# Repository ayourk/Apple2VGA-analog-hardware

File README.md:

# Clone of ∀2 Retro Computing Analog VGA Card & PicoPal

Design files for the ∀2 Analog series of VGA cards

## Description
Modified version of V2RetroComputing's Apple II Analog VGA Expansion Board using KiCAD 6.0.x. <br />
Changes from original:
* Moved solder jumpers to the back of the board for both the (lack of) PAL/GAL and non WiFi Pico.
* Reorganized Schematic to more easily generate a BOM with Part numbers from LSCS, DigiKey, and Mouser.
* Adopted Hans Hübner's VGA port connector break-away feature. Also reworked board to be 2 layers vs 4 layers but kept 4x bus transcievers vs Han's 2 since the chip in the 4x variant is easier to obtain.
* Added a PLCC socket for the PAL/GAL chip that is getting difficult to find.  Be sure to bridge the solder jumper on the back if you don't plan to populate this socket.
* Re-adjusted layout to provide more Analog VGA signal clarity by making the traces as short as possible between the VGA port connector and the PICO.
* Switched from IDC header style to a shielded FPC cable for less chance of signal interference when using the optional break-away feature.
* Rounded off PCB corners where it made sense.  I hate getting stabbed by PCBs (Grrrr)!

This board should still be binary compatible with the software this hardware was forked from.

### PCB Layout

### See Also
https://github.com/V2RetroComputing/analog <br />
https://github.com/ayourk/Apple2Analog-VGA <br />
https://github.com/hanshuebner/AppleII-VGA <br />
https://github.com/markadev/AppleII-VGA <br />
[Apple II Expansion Card Size Specifications](V2A-Rev1/docs/Apple_II_ExpansionCard_Spec.txt) <br />
[Apple II Expansion Slot Pinout](V2A-Rev1/docs/Apple2SlotPinout.html) <br />
[Apple II Hardware Reference](V2A-Rev1/docs/Apple2HardwareReference.pdf) <br />
https://github.com/ayourk/Apple2Proto <br />

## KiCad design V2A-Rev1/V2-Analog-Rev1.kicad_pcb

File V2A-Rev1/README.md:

# Apple2Proto
Design files for the ∀2 Analog series of VGA cards

## Description
Modified version of V2RetroComputing's Apple II Analog VGA Expansion Board using KiCAD 6.0.x. <br />
Changes from original:
* Moved solder jumpers to the back of the board for both the (lack of) PAL/GAL and non WiFi Pico.
* Reorganized Schematic to more easily generate a BOM with Part numbers from LSCS, DigiKey, and Mouser.
* Adopted Hans Hübner's VGA port connector break-away feature. Also reworked board to be 2 layers vs 4 layers but kept 4x bus transcievers vs Han's 2 since the chip in the 4x variant is easier to obtain.
* Added a PLCC socket for the PAL/GAL chip that is getting difficult to find.  Be sure to bridge the solder jumper on the back if you don't plan to populate this socket.
* Re-adjusted layout to provide more Analog VGA signal clarity by making the traces as short as possible between the VGA port connector and the PICO.
* Switched from IDC header style to a shielded FPC cable for less chance of signal interference when using the optional break-away feature.
* Rounded off PCB corners where it made sense.  I hate getting stabbed by PCBs (Grrrr)!

This board should still be binary compatible with the software this hardware was forked from.

### PCB Layout

### See Also
https://github.com/V2RetroComputing/analog <br />
https://github.com/ayourk/Apple2Analog-VGA <br />
https://github.com/hanshuebner/AppleII-VGA <br />
[Apple II Expansion Card Size Specifications](V2A-Rev1/docs/Apple_II_ExpansionCard_Spec.txt) <br />
[Apple II Expansion Slot Pinout](V2A-Rev1/docs/Apple2SlotPinout.html) <br />
[Apple II Hardware Reference](V2A-Rev1/docs/Apple2HardwareReference.pdf) <br />
https://github.com/ayourk/Apple2Proto <br />

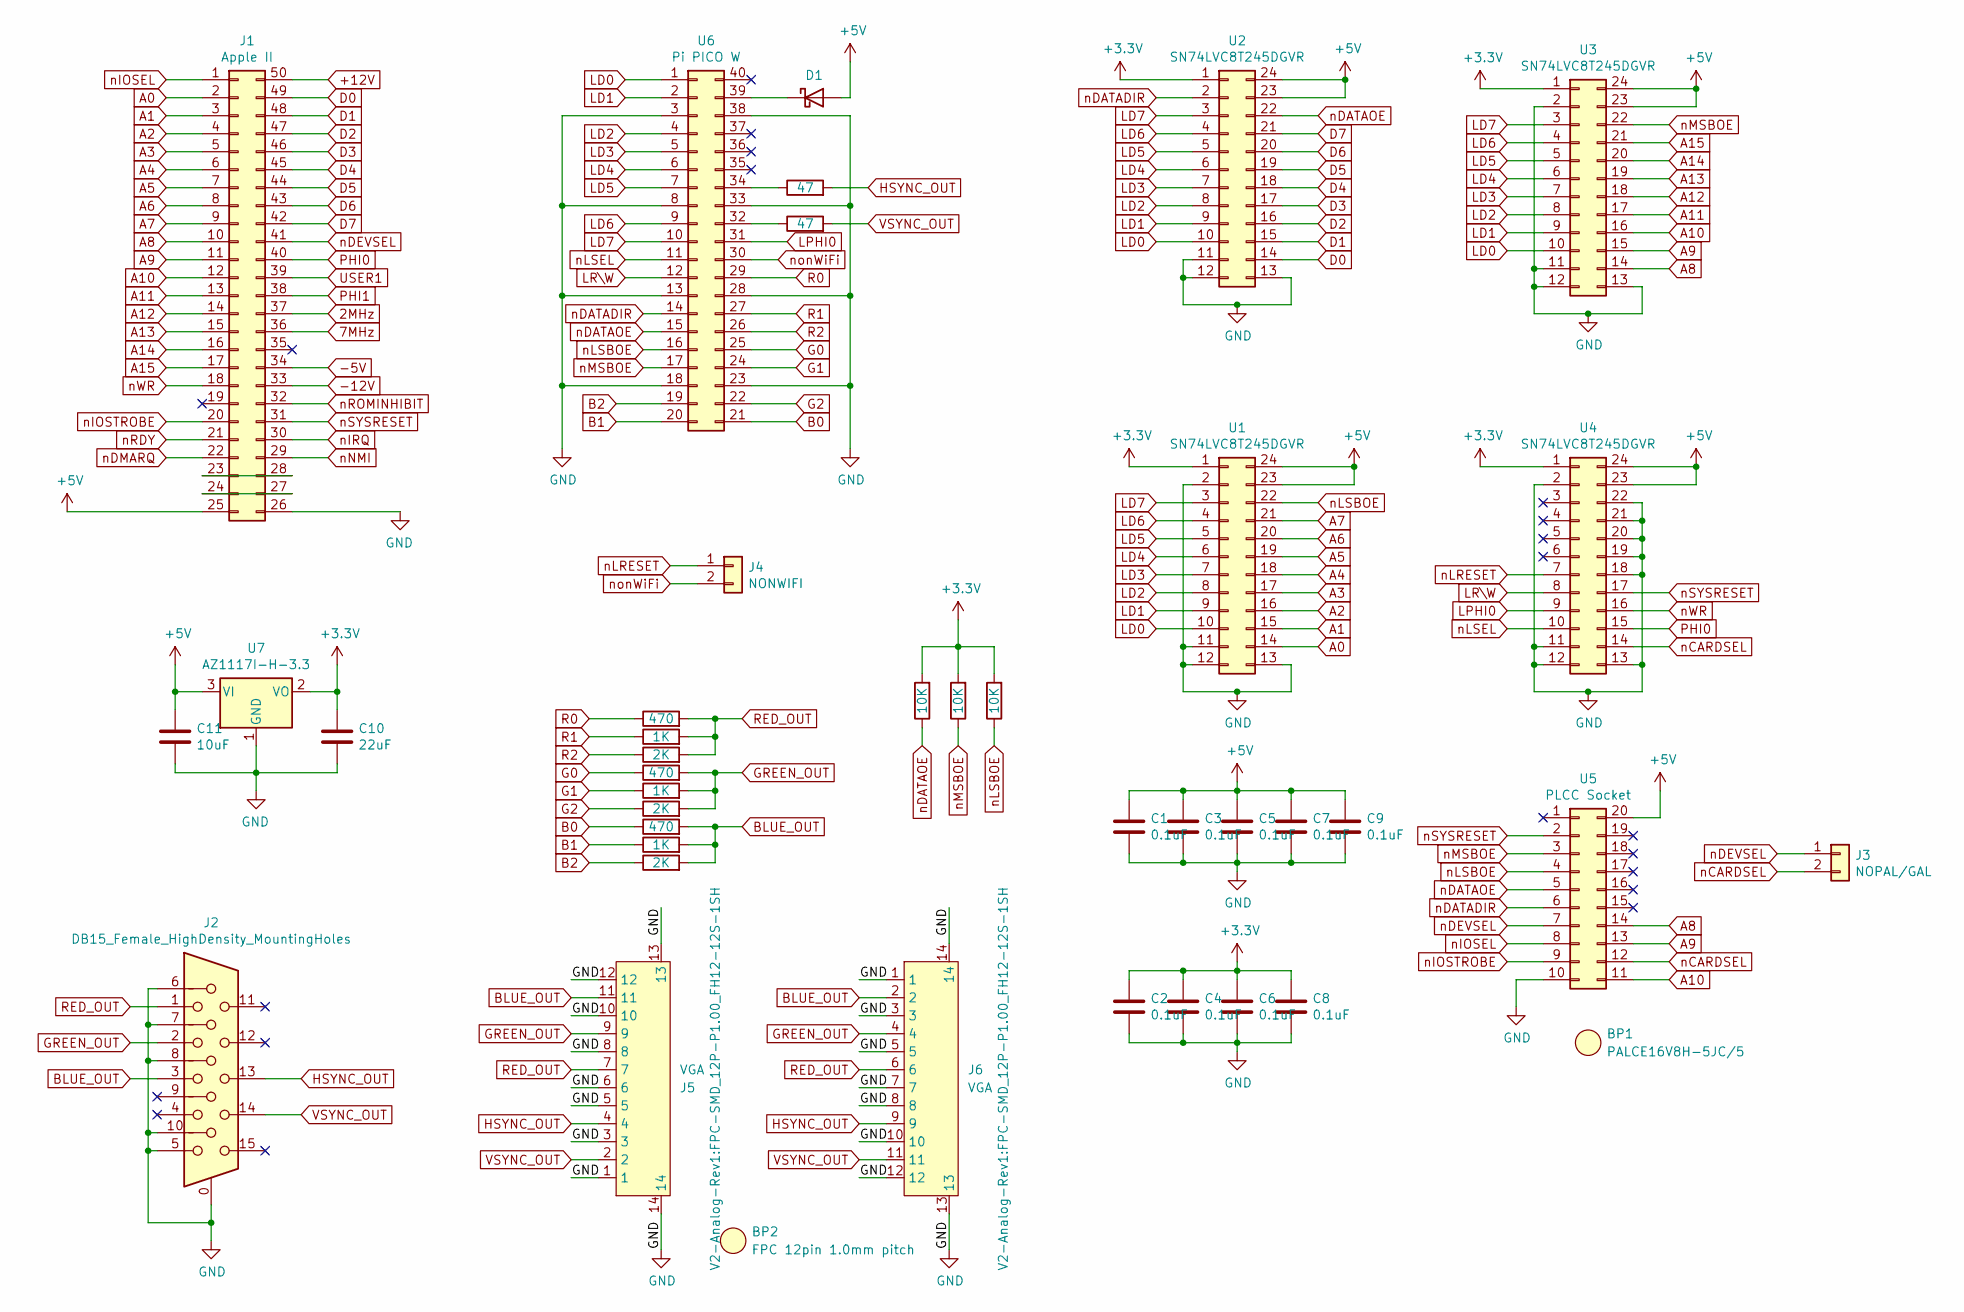
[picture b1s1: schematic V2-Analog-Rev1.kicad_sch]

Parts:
BP1: PALCE16V8H-5JC/5; BOM_Placeholder; MPN PALCE16V8H-5JC/5; LCSC C3292615
BP2: FPC 12pin 1.0mm pitch; BOM_Placeholder; MPN 0152670279; LCSC C18108667
C1, C2, C3, C4, C5, C6, C7, C8, C9: 0.1uF; C_0402_1005Metric_Pad0.74x0.62mm_HandSolder; MPN CL05B104KA5NNNC; LCSC C155422
C10: 22uF; C_0805_2012Metric_Pad1.18x1.45mm_HandSolder; MPN CL21A226MAYNNNE; LCSC C602037
C11: 10uF; C_0805_2012Metric_Pad1.18x1.45mm_HandSolder; MPN CL21A106KAYNNNE; LCSC C15850
D1: D_Schottky; D_SMA_Handsoldering; MPN SS14F; LCSC C64880
J1: Apple II; AppleII
J2: DB15_Female_HighDensity_MountingHoles; DSUB-15-HD_Female_Horizontal_P2.29x1.98mm_EdgePinOffset3.03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; MPN L77HDE15SD1CH4FVGA; LCSC C138387
J3: NOPAL/GAL; SolderJumper-2_P1.3mm_Open_TrianglePad1.0x1.5mm
J4: NONWIFI; SolderJumper-2_P1.3mm_Open_TrianglePad1.0x1.5mm
J5, J6: VGA; FPC-SMD_12P-P1.00_FH12-12S-1SH; MPN FH12-12S-1SH(55); LCSC C5148307
R1, R4, R7: 470; R_0402_1005Metric_Pad0.72x0.64mm_HandSolder; MPN ERJ-2RKF4700X; LCSC C413076
R2, R5, R8: 1K; R_0402_1005Metric_Pad0.72x0.64mm_HandSolder; MPN ERJ-2RKF1001X; LCSC C242161
R3, R6, R9: 2K; R_0402_1005Metric_Pad0.72x0.64mm_HandSolder; MPN ERJ-2RKF2001X; LCSC C413086
R10, R11: 47; R_0402_1005Metric_Pad0.72x0.64mm_HandSolder; MPN ERJ-2RKF47R0X; LCSC C413056
R12, R13, R14: 10K; R_0603_1608Metric_Pad0.98x0.95mm_HandSolder; MPN ERJ-3EKF1002V; LCSC C191124
U1, U2, U3, U4: SN74LVC8T245DGVR; TSSOP-24_4.4x5mm_P0.4mm; MPN SN74LVC8T245DGVR; LCSC C364886
U5: PLCC Socket; A-CCS_020-Z-SM_SMD-Socket; MPN A-CCS 020-Z-SM; LCSC C7058802
U6: Pi PICO W; DIP-40_W16.51mm_SMDSocket_LongPads; MPN SC0918; LCSC C7203003
U7: AZ1117I-H-3.3; SOT-223-3_TabPin2; MPN AZ1117H-3.3TRG1; LCSC C110474

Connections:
2MHz: J1.37
7MHz: J1.36
+3V3: C2.1, C4.1, C6.1, C8.1, C10.1, R12.2, R13.2, R14.2, U1.1, U2.1, U3.1, U4.1, U7.2 (VO)
+5V: C1.1, C3.1, C5.1, C7.1, C9.1, C11.1, D1.2 (A), J1.25, U1.23, U1.24, U2.23, U2.24, U3.23, U3.24, U4.23, U4.24, U5.20, U7.3 (VI)
+12V: J1.50
-5V: J1.34
-12V: J1.33
A0: J1.2, U1.14
A1: J1.3, U1.15
A2: J1.4, U1.16
A3: J1.5, U1.17
A4: J1.6, U1.18
A5: J1.7, U1.19
A6: J1.8, U1.20
A7: J1.9, U1.21
A8: J1.10, U3.14, U5.14
A9: J1.11, U3.15, U5.13
A10: J1.12, U3.16, U5.11
A11: J1.13, U3.17
A12: J1.14, U3.18
A13: J1.15, U3.19
A14: J1.16, U3.20
A15: J1.17, U3.21
B0: R7.1, U6.21
B1: R8.1, U6.20
B2: R9.1, U6.19
BLUE_OUT: J2.3, J5.11, J6.2, R7.2, R8.2, R9.2
D0: J1.49, U2.14
D1: J1.48, U2.15
D2: J1.47, U2.16
D3: J1.46, U2.17
D4: J1.45, U2.18
D5: J1.44, U2.19
D6: J1.43, U2.20
D7: J1.42, U2.21
G0: R4.1, U6.25
G1: R5.1, U6.24
G2: R6.1, U6.22
GND: C1.2, C2.2, C3.2, C4.2, C5.2, C6.2, C7.2, C8.2, C9.2, C10.2, C11.2, J1.26, J2.0, J2.5, J2.6, J2.7, J2.8, J2.10, J5.1, J5.3, J5.5, J5.6, J5.8, J5.10, J5.12, J5.13, J5.14, J6.1, J6.3, J6.5, J6.7, J6.8, J6.10, J6.12, J6.13, J6.14, U1.2, U1.11, U1.12, U1.13, U2.11, U2.12, U2.13, U3.2, U3.11, U3.12, U3.13, U4.2, U4.11, U4.12, U4.13, U4.18, U4.19, U4.20, U4.21, U4.22, U5.10, U6.3, U6.8, U6.13, U6.18, U6.23, U6.28, U6.33, U6.38, U7.1 (GND)
GREEN_OUT: J2.2, J5.9, J6.4, R4.2, R5.2, R6.2
HSYNC_OUT: J2.13, J5.4, J6.9, R10.2
LD0: U1.10, U2.10, U3.10, U6.1
LD1: U1.9, U2.9, U3.9, U6.2
LD2: U1.8, U2.8, U3.8, U6.4
LD3: U1.7, U2.7, U3.7, U6.5
LD4: U1.6, U2.6, U3.6, U6.6
LD5: U1.5, U2.5, U3.5, U6.7
LD6: U1.4, U2.4, U3.4, U6.9
LD7: U1.3, U2.3, U3.3, U6.10
LPHI0: U4.9, U6.31
LR\W: U4.8, U6.12
unnamed: D1.1 (K), U6.39
unnamed: J1.23, J1.28
unnamed: J1.24, J1.27
unnamed: R10.1, U6.34
unnamed: R11.1, U6.32
PHI0: J1.40, U4.15
PHI1: J1.38
R0: R1.1, U6.29
R1: R2.1, U6.27
R2: R3.1, U6.26
RED_OUT: J2.1, J5.7, J6.6, R1.2, R2.2, R3.2
USER1: J1.39
VSYNC_OUT: J2.14, J5.2, J6.11, R11.2
nCARDSEL: J3.2, U4.14, U5.12
nDATADIR: U2.2, U5.6, U6.14
nDATAOE: R12.1, U2.22, U5.5, U6.15
nDEVSEL: J1.41, J3.1, U5.7
nDMARQ: J1.22
nIOSEL: J1.1, U5.8
nIOSTROBE: J1.20, U5.9
nIRQ: J1.30
nLRESET: J4.1, U4.7
nLSBOE: R14.1, U1.22, U5.4, U6.16
nLSEL: U4.10, U6.11
nMSBOE: R13.1, U3.22, U5.3, U6.17
nNMI: J1.29
nRDY: J1.21
nROMINHIBIT: J1.32
nSYSRESET: J1.31, U4.17, U5.2
nWR: J1.18, U4.16
nonWiFi: J4.2, U6.30

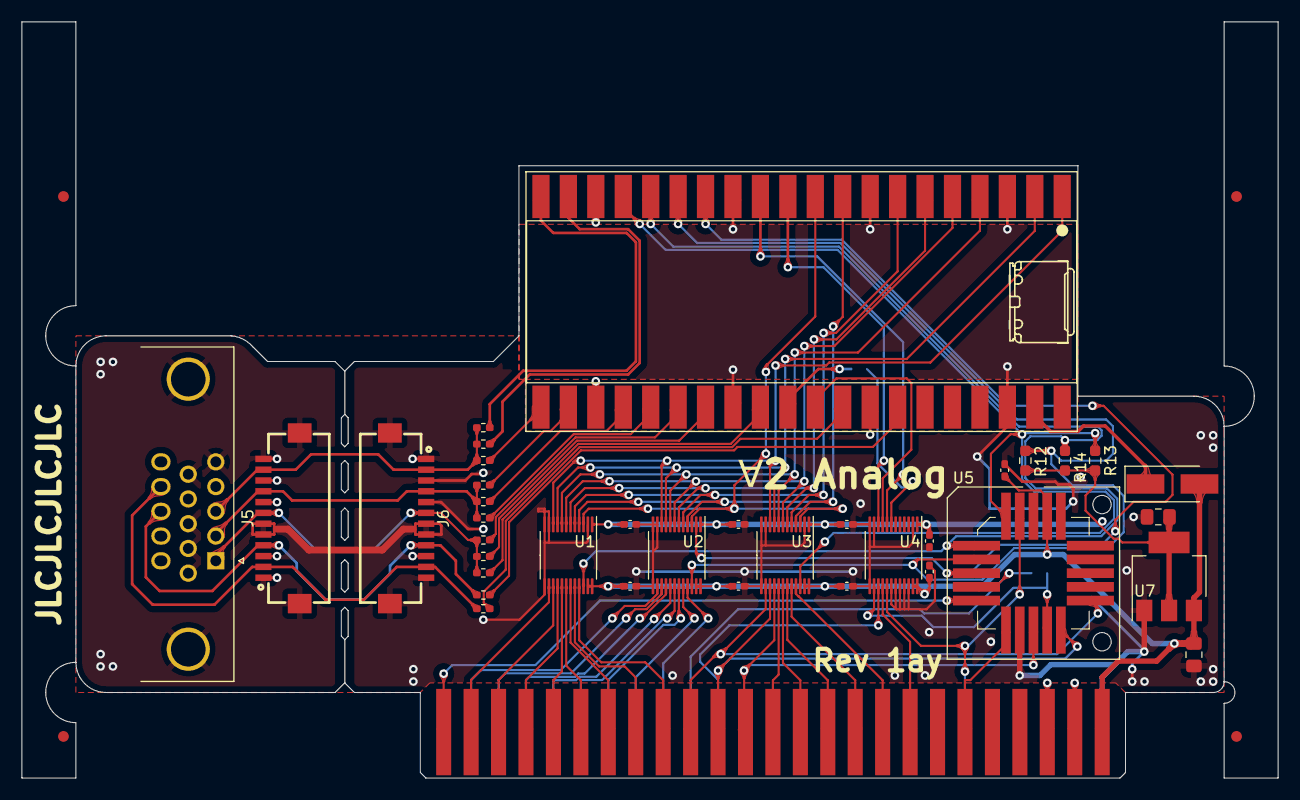
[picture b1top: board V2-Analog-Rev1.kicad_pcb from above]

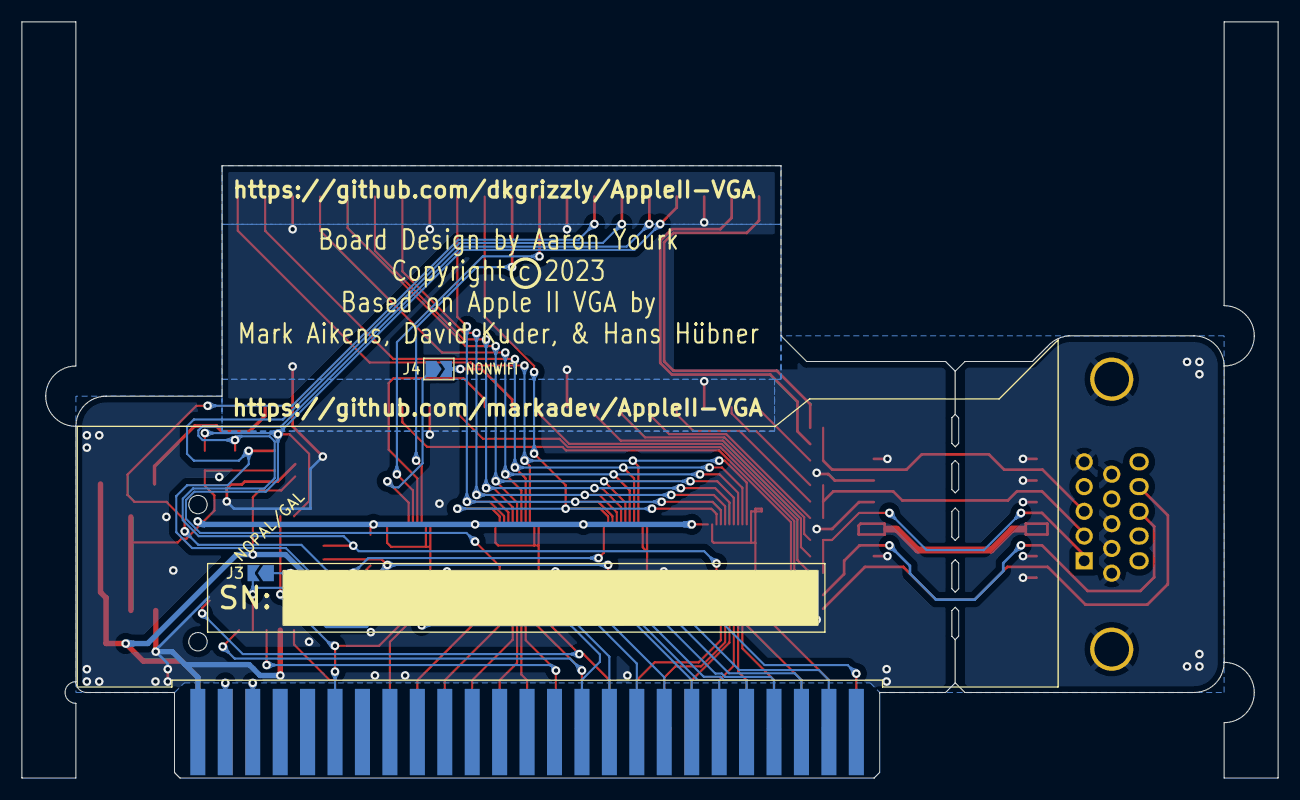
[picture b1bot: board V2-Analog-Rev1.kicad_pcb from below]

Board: 2 copper layers, 116.2 x 69.9 mm, 41 parts (2 on the bottom side), 70 nets.

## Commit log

2024-04-15 My reinterpretation of V2RetroComputing's Analog VGA Board.
2024-04-15 Update design to use a PLCC socket for PAL/GAL.
2024-04-21 Added socket for PLCC. Reorganized layout for improved VGA picture clarity.
2024-04-21 Added README and other documentation.
2024-04-21 It might help to put the README in the right spot.
2024-05-15 Added Left and Right Fiducial break away Rails
2024-05-21 Fix issues with JLCPCB manufacturing standards.
2024-05-24 Added V-scoring suggestion to VGA break-away port. Added to Silkscreen MicroUSB port location from PICO.
2024-05-24 Update README.md
    Fix errorneous title.
